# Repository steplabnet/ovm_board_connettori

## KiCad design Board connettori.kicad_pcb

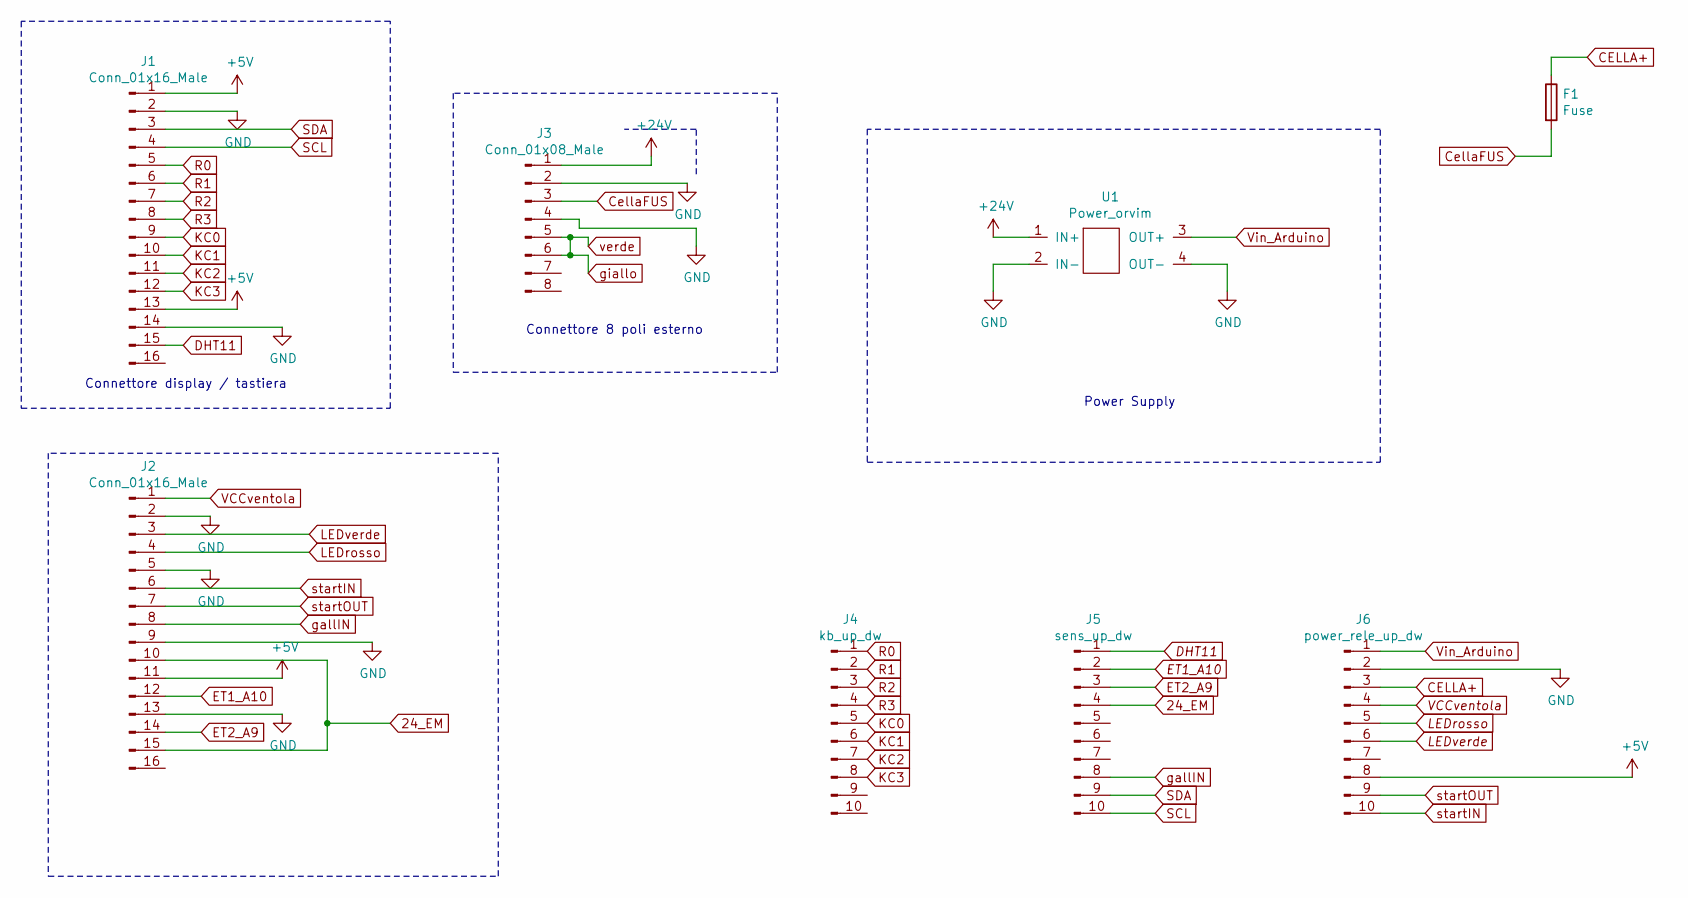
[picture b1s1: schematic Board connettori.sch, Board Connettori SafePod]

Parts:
F1: Fuse; fusibile_18mm
J1, J2: Conn_01x16_Male; Phoenix_1829471
J3: Conn_01x08_Male; Phoenix_1829471_8pin
J4: kb_up_dw; PinSocket_1x10_P2.54mm_Vertical
J5: sens_up_dw; PinSocket_1x10_P2.54mm_Vertical
J6: power_rele_up_dw; PinSocket_1x10_P2.54mm_Vertical
U1: Power_orvim

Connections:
24_EM: J2.10, J2.15, J5.4
+5V: J1.1, J1.13, J2.11, J6.8
+24V: J3.1, U1.1 (IN+)
CELLA+: F1.1, J6.3
CellaFUS: F1.2, J3.3
DHT11: J1.15, J5.1
ET1_A10: J2.12, J5.2
ET2_A9: J2.14, J5.3
GND: J1.2, J1.14, J2.2, J2.5, J2.9, J2.13, J3.2, J3.4, J6.2, U1.2 (IN-), U1.4 (OUT-)
KC0: J1.9, J4.5
KC1: J1.10, J4.6
KC2: J1.11, J4.7
KC3: J1.12, J4.8
LEDrosso: J2.4, J6.5
LEDverde: J2.3, J6.6
R0: J1.5, J4.1
R1: J1.6, J4.2
R2: J1.7, J4.3
R3: J1.8, J4.4
SCL: J1.4, J5.10
SDA: J1.3, J5.9
VCCventola: J2.1, J6.4
Vin_Arduino: J6.1, U1.3 (OUT+)
gallIN: J2.8, J5.8
giallo: J3.5, J3.6
startIN: J2.6, J6.10
startOUT: J2.7, J6.9

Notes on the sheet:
Connettore 8 poli esterno
Connettore display / tastiera
Power Supply

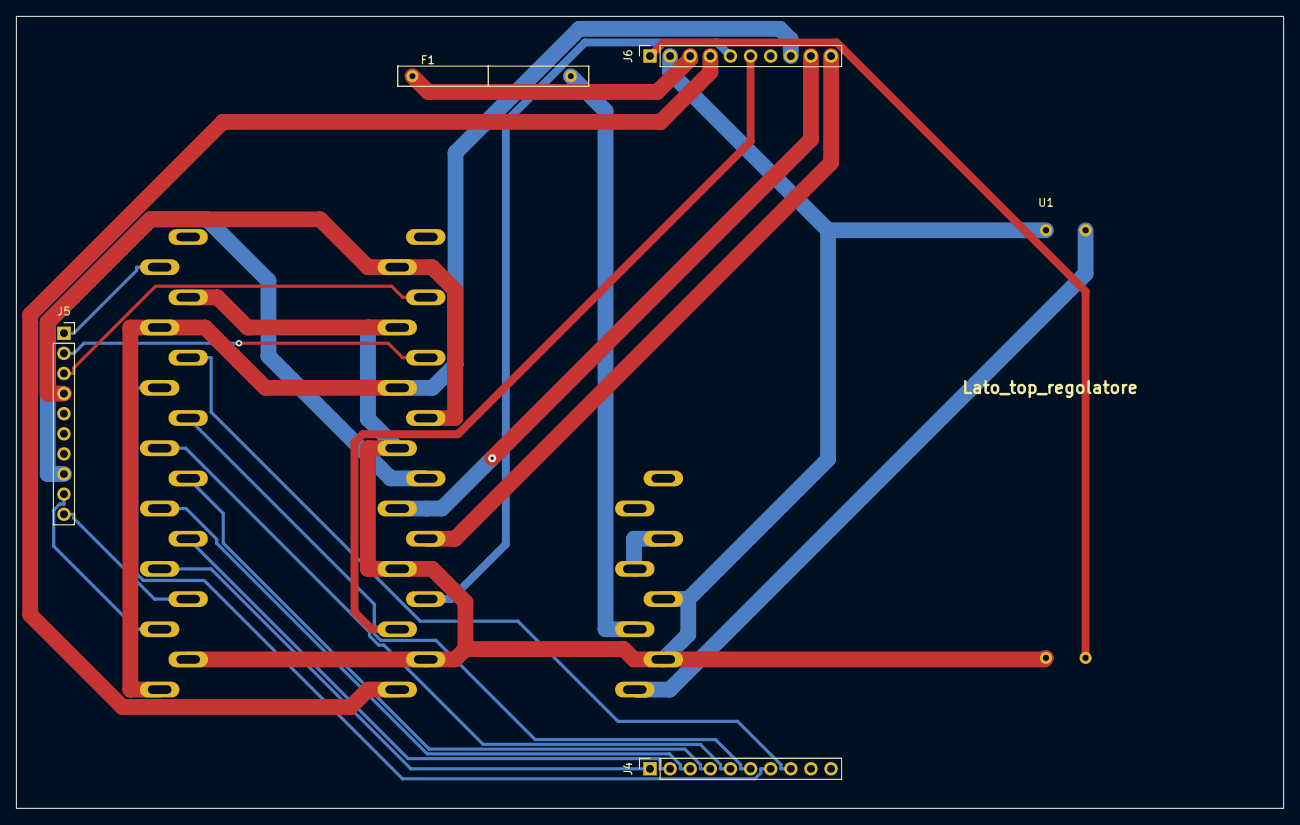
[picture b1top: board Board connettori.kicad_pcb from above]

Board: 2 copper layers, 160.0 x 100.0 mm, 8 parts (0 on the bottom side), 27 nets.
